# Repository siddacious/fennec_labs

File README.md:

# Fennec Studios Hamtonio
This is a 'lil board for building into toys. It has:
- Atmel ATSAMD51G19 Cortex m4 processor
- A TPS61029-powered boost converter to run off of batteries
- SWD debug connector
- Winbond 25Q16VJV 2 MB QSPI Flash
- More peripherals than you can throw a stick at
- Runs Circuit Python

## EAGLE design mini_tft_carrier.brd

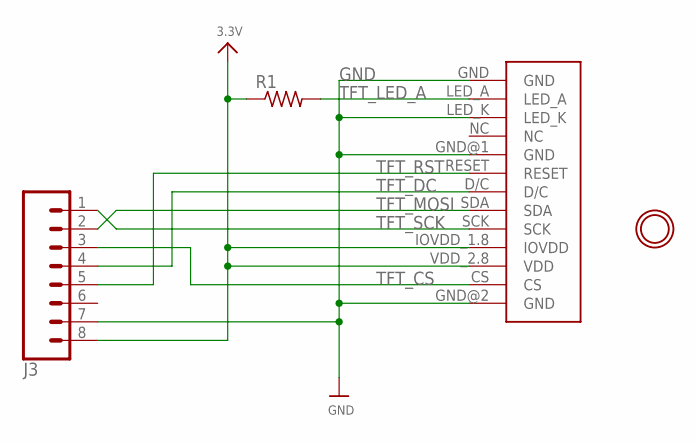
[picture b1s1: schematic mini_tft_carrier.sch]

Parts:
J3: CONN_08NO_SILK_FEMALE_PTH; 1X08_NO_SILK
R1: R-US_R0603; R0603
U$1: MICRO_TFT
U$2: MOUNTINGHOLE2.5; MOUNTINGHOLE_2.5_PLATED

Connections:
3.3V: J3.8, R1.1, U$1.IOVDD_1.8 (IOVDD), U$1.VDD_2.8 (VDD)
GND: J3.7, U$1.GND, U$1.GND@1 (GND), U$1.GND@2 (GND), U$1.LED_K
TFT_CS: J3.3, U$1.CS
TFT_DC: J3.4, U$1.D/C
TFT_LED_A: R1.2, U$1.LED_A
TFT_MOSI: J3.2, U$1.SDA
TFT_RST: J3.5, U$1.RESET
TFT_SCK: J3.1, U$1.SCK

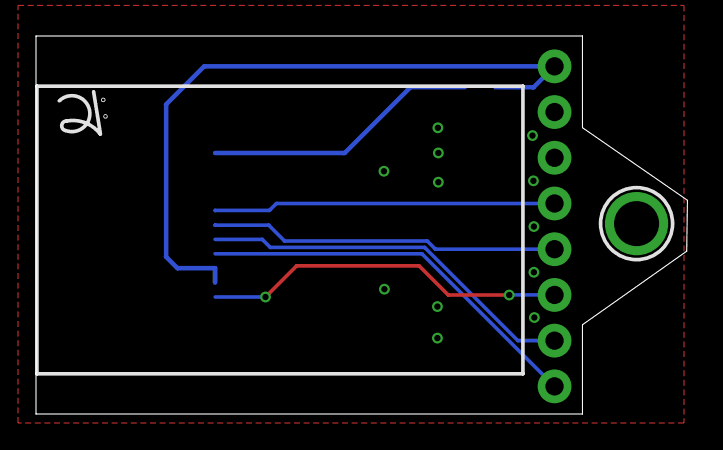
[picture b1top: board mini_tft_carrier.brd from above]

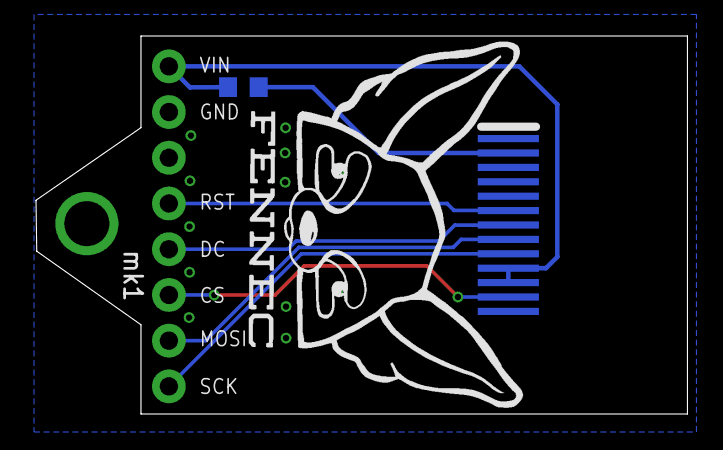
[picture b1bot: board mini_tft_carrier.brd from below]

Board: 2 copper layers, 36.2 x 21.0 mm, 4 parts (2 on the bottom side), 8 nets.

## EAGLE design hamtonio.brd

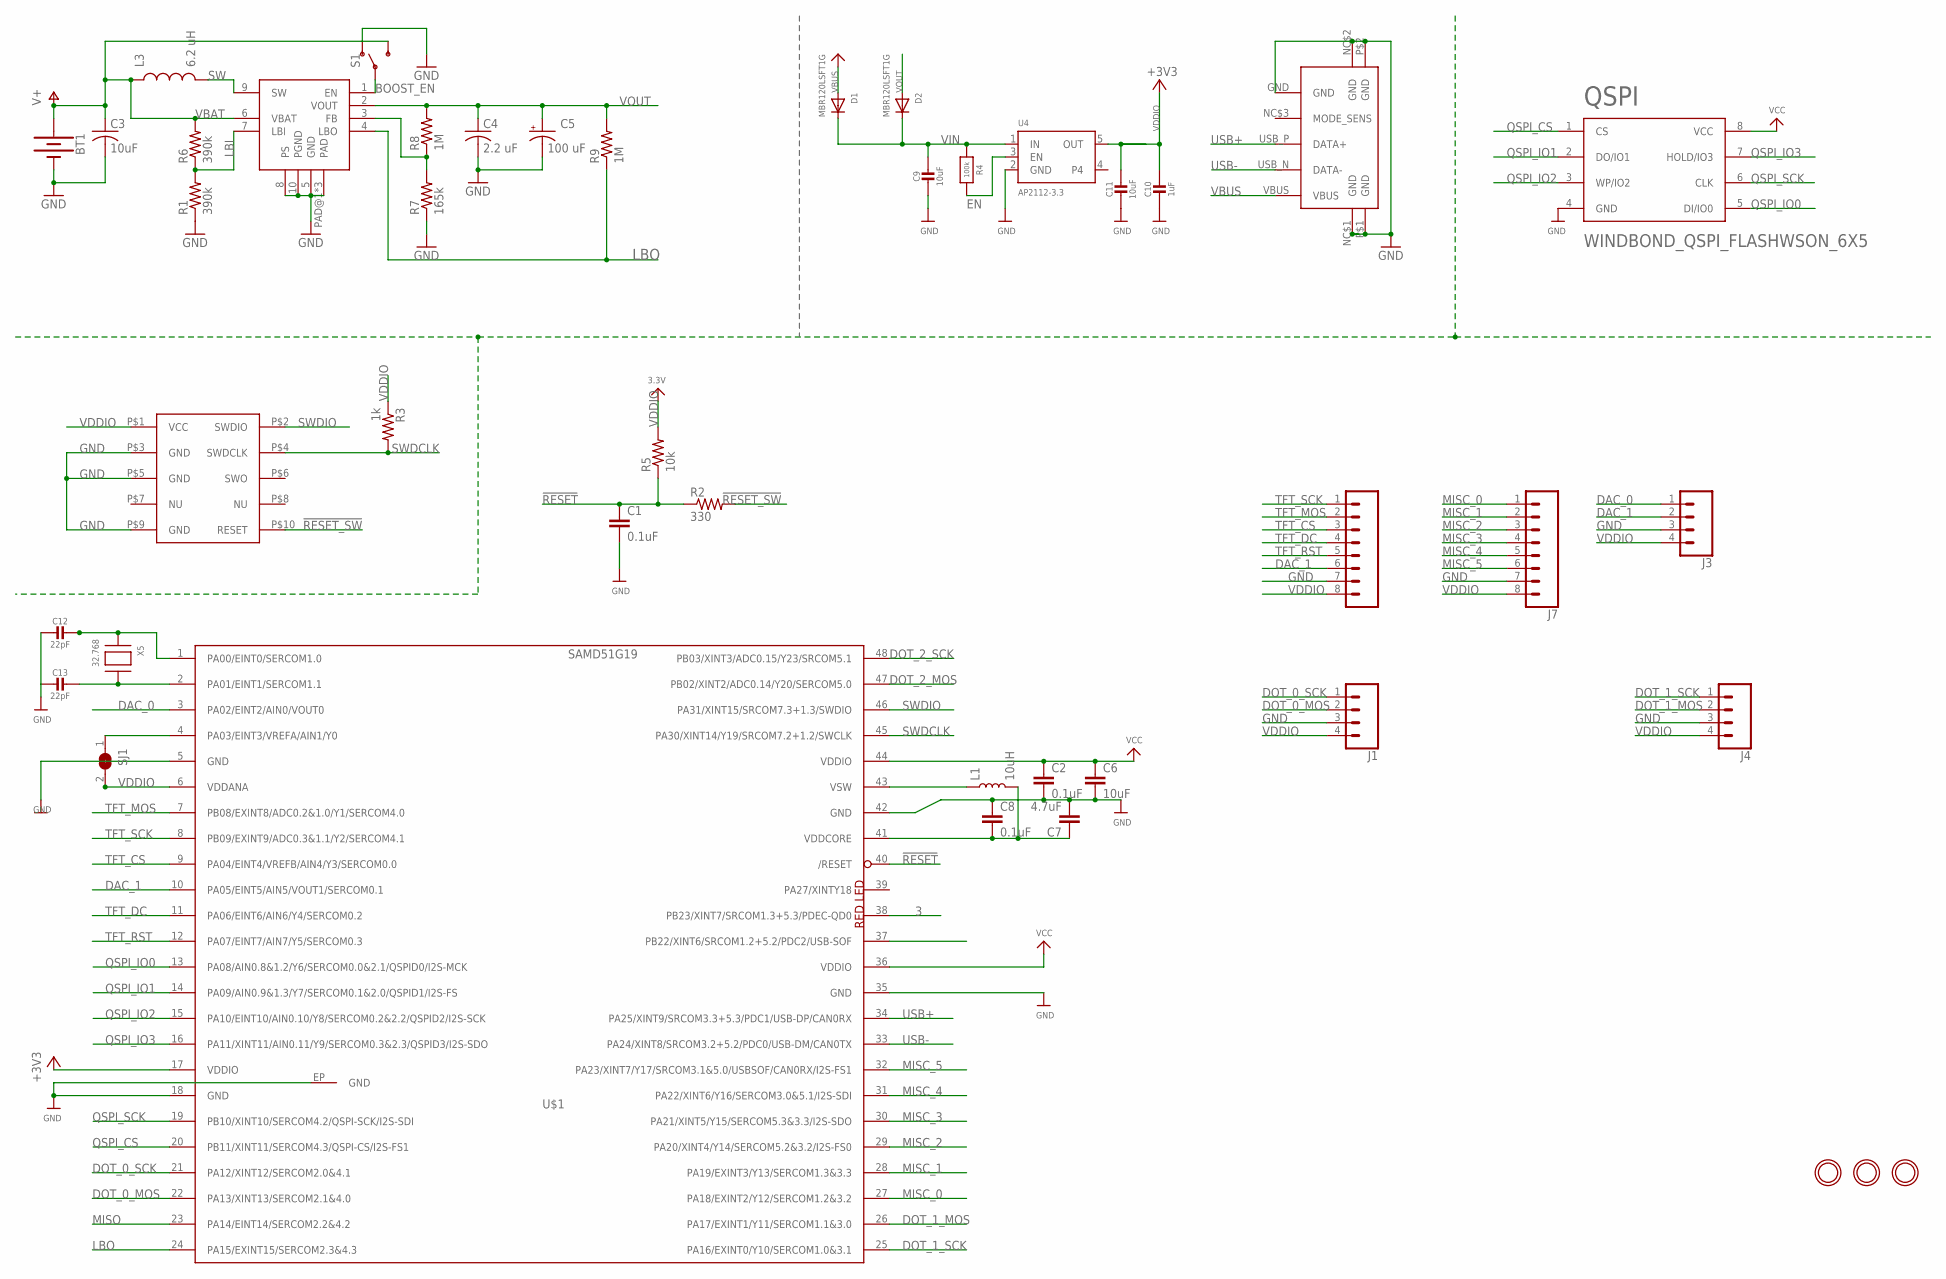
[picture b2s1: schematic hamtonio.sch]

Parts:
BT1: BATTERYDUAL_AA_XX; DUAL_AA
C1, C2, C8: 0.1uF; 0603
C3: 10uF; C0805K
C4: 2.2 uF; C0805K
C5: 100 uF; CT6032
C6: 10uF; 0805
C7: 4.7uF; 0603
C9, C11: 10uF; 0805-NO
C10: 1uF; 0603-NO
C12, C13: 22pF; 0603-NO
D1, D2: MBR120LSFT1G; SOD-123
J1, J3, J4: CONN_041X04_NO_SILK; 1X04_NO_SILK
J6, J7: CONN_08NO_SILK_FEMALE_PTH; 1X08_NO_SILK
L1: 10uH; 1007_INDUCTOR
L3: 6.2 uH; CDRH52D
QSPI: WINDBOND_QSPI_FLASHWSON_6X5; WSON_6X5MM
R1, R6: 390k; R0603
R2: 330; R0603
R3: 1k; R0603
R4: 100k; 0603-NO
R5: 10k; R0603
R7: 165k; R0603
R8, R9: 1M; R0603
S1: SWITCH-SPDTSMD_C&K_JS; SPDT_SMD
SJ1: SOLDERJUMPERCLOSED; SOLDERJUMPER_CLOSEDWIRE
U4: AP2112-3.3; SOT23-5
U$1: SAMD51G19; QFN-48
U$2: SWD_HEADER; AMPHENOL_SWD
U$8: TPS61029
U$12: AMPHENOL_MICRO_USBAMPHENOL_MICRO_USB_BETTER; BETTER_AMP_MICRO_USB
U$22, U$34, U$39: MOUNTINGHOLE2.5; MOUNTINGHOLE_2.5_PLATED
X5: 32.768; XTAL3215

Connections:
3: U$1.38 (PB23/XINT7/SRCOM1.3+5.3/PDEC-QD0)
!RESET: C1.1, R2.1, R5.1, U$1.40 (/RESET)
!RESET_SW: R2.2, U$2.P$10 (RESET)
AREF: SJ1.1, U$1.4 (PA03/EINT3/VREFA/AIN1/Y0)
BOOST_EN: S1.P$2, S1.P$5, U$8.1 (EN)
DAC_0: J3.1, U$1.3 (PA02/EINT2/AIN0/VOUT0)
DAC_1: J3.2, J6.6, U$1.10 (PA05/EINT5/AIN5/VOUT1/SERCOM0.1)
DOT_0_MOS: J1.2, U$1.22 (PA13/XINT13/SERCOM2.1&4.0)
DOT_0_SCK: J1.1, U$1.21 (PA12/XINT12/SERCOM2.0&4.1)
DOT_1_MOS: J4.2, U$1.26 (PA17/EXINT1/Y11/SERCOM1.1&3.0)
DOT_1_SCK: J4.1, U$1.25 (PA16/EXINT0/Y10/SERCOM1.0&3.1)
DOT_2_MOS: U$1.47 (PB02/XINT2/ADC0.14/Y20/SERCOM5.0)
DOT_2_SCK: U$1.48 (PB03/XINT3/ADC0.15/Y23/SRCOM5.1)
EN: R4.2, U4.3 (EN)
FB: R7.2, R8.1, U$8.3 (FB)
GND: BT1.V- (-), C1.2, C2.2, C3.2, C4.2, C5.-, C6.2, C7.2, C8.1, C9.2, C10.2, C11.2, C12.2, C13.2, J1.3, J3.3, J4.3, J6.7, J7.7, QSPI.4 (GND), R1.1, R7.1, S1.P$1 (O), S1.P$6 (O), U4.2 (GND), U$1.5 (GND), U$1.18 (GND), U$1.35 (GND), U$1.42 (GND), U$1.EP (GND), U$2.P$3 (GND), U$2.P$5 (GND), U$2.P$9 (GND), U$8.5 (GND), U$8.8 (PS), U$8.10 (PGND), U$8.PAD@1 (PAD), U$8.PAD@2 (PAD), U$8.PAD@3 (PAD), U$12.GND, U$12.NC$1 (GND), U$12.NC$2 (GND), U$12.P$1 (GND), U$12.P$2 (GND)
LBI: R1.2, R6.1, U$8.7 (LBI)
LBO: R9.1, U$1.24 (PA15/EXINT15/SERCOM2.3&4.3), U$8.4 (LBO)
MISC_0: J7.1, U$1.27 (PA18/EXINT2/Y12/SERCOM1.2&3.2)
MISC_1: J7.2, U$1.28 (PA19/EXINT3/Y13/SERCOM1.3&3.3)
MISC_2: J7.3, U$1.29 (PA20/XINT4/Y14/SERCOM5.2&3.2/I2S-FS0)
MISC_3: J7.4, U$1.30 (PA21/XINT5/Y15/SERCOM5.3&3.3/I2S-SDO)
MISC_4: J7.5, U$1.31 (PA22/XINT6/Y16/SERCOM3.0&5.1/I2S-SDI)
MISC_5: J7.6, U$1.32 (PA23/XINT7/Y17/SRCOM3.1&5.0/USBSOF/CAN0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)
MISO: U$1.23 (PA14/EINT14/SERCOM2.2&4.2)
QSPI_CS: QSPI.1 (CS), U$1.20 (PB11/XINT11/SERCOM4.3/QSPI-CS/I2S-FS1)
QSPI_IO0: QSPI.5 (DI/IO0), U$1.13 (PA08/AIN0.8&1.2/Y6/SERCOM0.0&2.1/QSPID0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)
QSPI_IO1: QSPI.2 (DO/IO1), U$1.14 (PA09/AIN0.9&1.3/Y7/SERCOM0.1&2.0/QSPID1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)
QSPI_IO2: QSPI.3 (WP/IO2), U$1.15 (PA10/EINT10/AIN0.10/Y8/SERCOM0.2&2.2/QS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)
QSPI_IO3: QSPI.7 (HOLD/IO3), U$1.16 (PA11/XINT11/AIN0.11/Y9/SERCOM0.3&2.3/QS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)
QSPI_SCK: QSPI.6 (CLK), U$1.19 (PB10/XINT10/SERCOM4.2/QSPI-SCK/I2S-SDI)
SW: L3.2, U$8.9 (SW)
SWDCLK: R3.2, U$1.45 (PA30/XINT14/Y19/SRCOM7.2+1.2/SWCLK), U$2.P$4 (SWDCLK)
SWDIO: U$1.46 (PA31/XINT15/SRCOM7.3+1.3/SWDIO), U$2.P$2 (SWDIO)
TFT_CS: J6.3, U$1.9 (PA04/EINT4/VREFB/AIN4/Y3/SERCOM0.0)
TFT_DC: J6.4, U$1.11 (PA06/EINT6/AIN6/Y4/SERCOM0.2)
TFT_MOS: J6.2, U$1.7 (PB08/EXINT8/ADC0.2&1.0/Y1/SERCOM4.0)
TFT_RST: J6.5, U$1.12 (PA07/EINT7/AIN7/Y5/SERCOM0.3)
TFT_SCK: J6.1, U$1.8 (PB09/EXINT9/ADC0.3&1.1/Y2/SERCOM4.1)
USB+: U$1.34 (PA25/XINT9/SRCOM3.3+5.3/PDC1/USB-DP/CAN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), U$12.USB_P (DATA+)
USB-: U$1.33 (PA24/XINT8/SRCOM3.2+5.2/PDC0/USB-DM/CAN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), U$12.USB_N (DATA-)
VBAT: BT1.V+ (+), C3.1, L3.1, R6.2, S1.P$3 (S), S1.P$4 (S), U$8.6 (VBAT)
VBUS: D1.A, U$12.VBUS
VDDCORE: C7.1, C8.2, L1.P$2 (2), U$1.41 (VDDCORE)
VDDIO: C2.1, C6.1, C10.1, C11.1, J1.4, J3.4, J4.4, J6.8, J7.8, QSPI.8 (VCC), R3.1, R5.2, SJ1.2, U4.5 (OUT), U$1.6 (VDDANA), U$1.17 (VDDIO), U$1.36 (VDDIO), U$1.44 (VDDIO), U$2.P$1 (VCC)
VIN: C9.1, D1.C, D2.C, R4.1, U4.1 (IN)
VOUT: C4.1, C5.+, D2.A, R8.2, R9.2, U$8.2 (VOUT)
VSW: L1.P$1 (1), U$1.43 (VSW)
XOSC32_A: C12.1, U$1.1 (PA00/EINT0/SERCOM1.0), X5.P$1
XOSC32_B: C13.1, U$1.2 (PA01/EINT1/SERCOM1.1), X5.P$2

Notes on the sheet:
RED LED

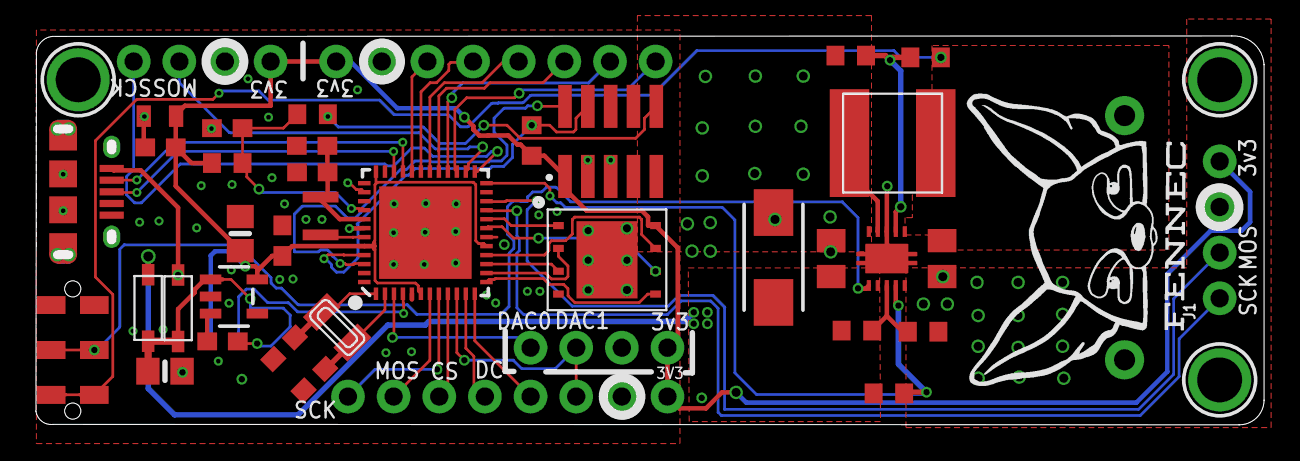
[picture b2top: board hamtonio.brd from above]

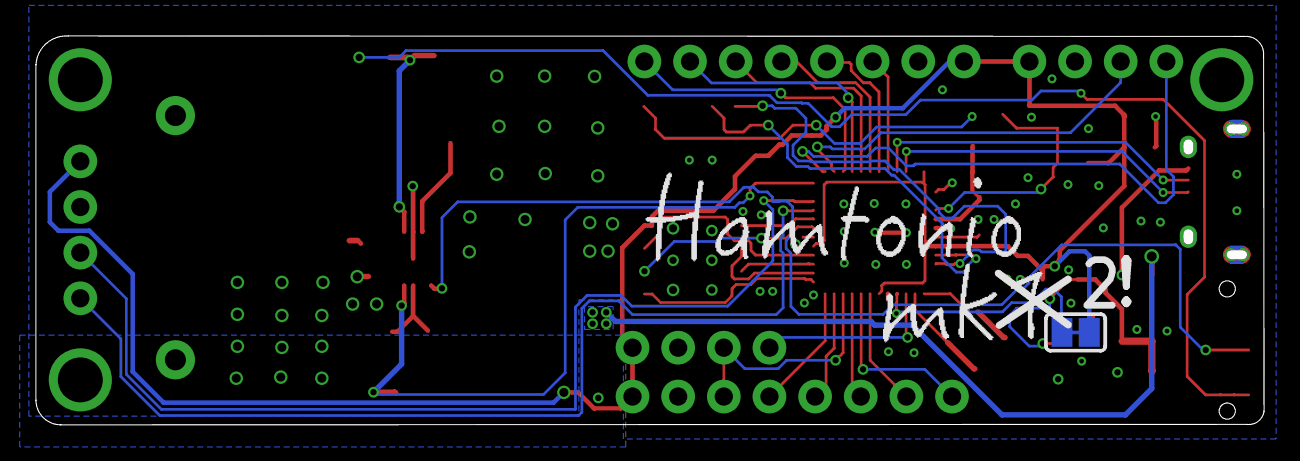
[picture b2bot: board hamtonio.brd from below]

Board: 2 copper layers, 67.8 x 21.1 mm, 44 parts (2 on the bottom side), 46 nets.

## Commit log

2018-10-27 first working commit; OSH Park 8J7wCeam
2018-10-27 tft carrier v1
2018-10-31 tft carrier and hamtonio mkx2; Oshpark MKiCLdFX
2018-12-16 backin' up

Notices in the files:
parts and their libraries:
SparkFun-Capacitors: Licensing: Creative Commons ShareAlike 4.0 International - https://creativecommons.org/licenses/by-sa/4.0
microbuilder: This work is placed in the public domain, and may be freely used for commercial and non-commercial work with the following conditions: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
